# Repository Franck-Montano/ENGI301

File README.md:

# ENGI301
Repository for ENGI301 course work.

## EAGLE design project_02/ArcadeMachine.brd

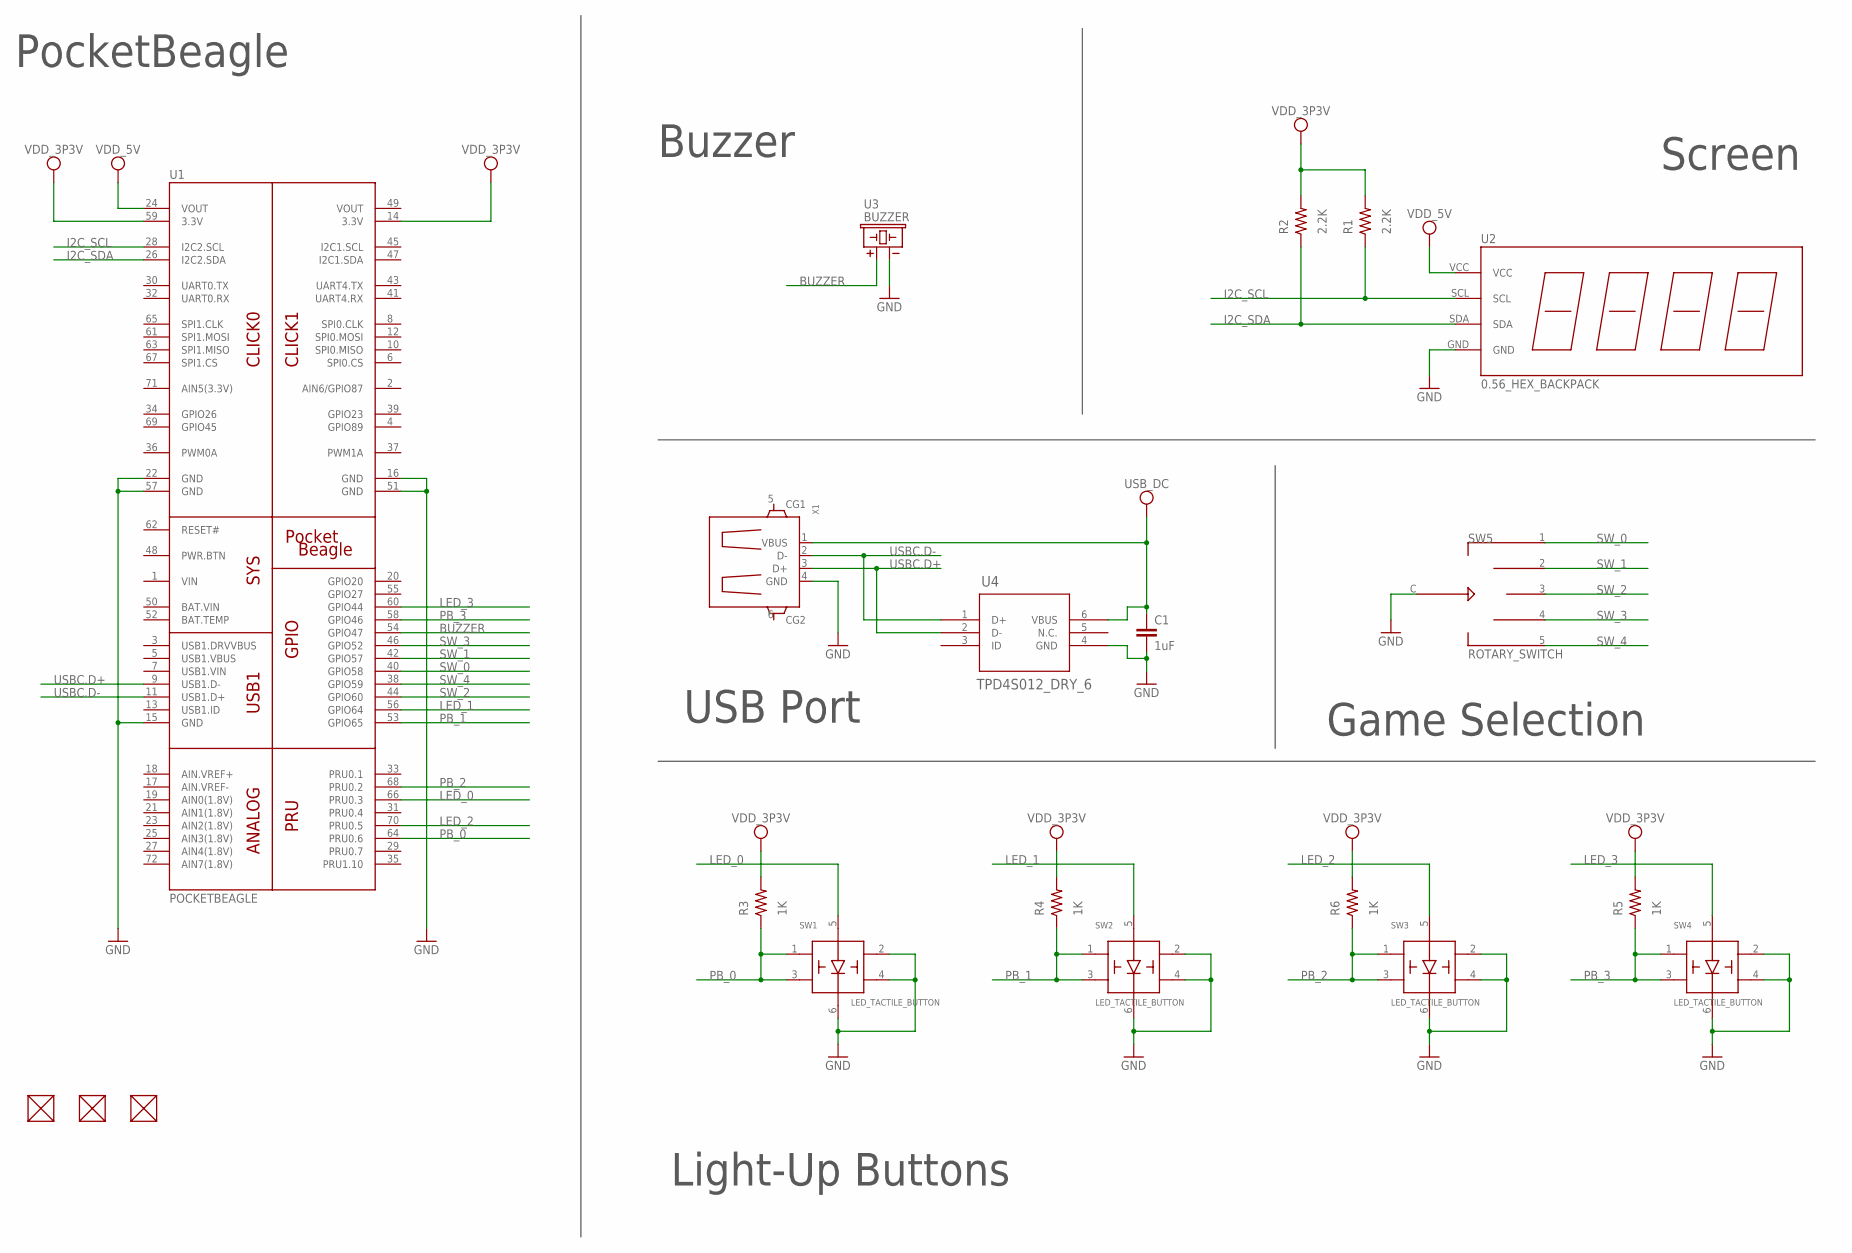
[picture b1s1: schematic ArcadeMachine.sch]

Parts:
C1: 1uF; SPARKFUN-CAPACITORS_0603-CAP
FUD1, FUD2, FUD3: FIDUCIAL; FIDUCIAL_40MIL
R1, R2: 2.2K; R0603
R3, R4, R5, R6: 1K; R0603
SW1, SW2, SW3, SW4: LED_TACTILE_BUTTON
SW5: ROTARY_SWITCH
U1: POCKETBEAGLE
U2: 0.56_HEX_BACKPACK
U3: BUZZER; BUZZER_6.5MM
U4: TPD4S012_DRY_6; BEAGLEBONE_BLUE_DRY6
X1: GHI2_USB_HOST_W/CHASSIS_GND; GHI2_USB_HOST_HORIZONTAL_W/CHASSIS_GND

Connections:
BAT.VIN: U1.50 (BAT.VIN)
BUZZER: U1.54 (GPIO47), U3.+
GND: C1.2, SW1.2, SW1.4, SW1.6, SW2.2, SW2.4, SW2.6, SW3.2, SW3.4, SW3.6, SW4.2, SW4.4, SW4.6, SW5.C, U1.15 (GND), U1.16 (GND), U1.22 (GND), U1.51 (GND), U1.57 (GND), U2.GND, U3.-, U4.4 (GND), X1.4 (GND)
I2C_SCL: R1.1, U1.28 (I2C2.SCL), U2.SCL
I2C_SDA: R2.1, U1.26 (I2C2.SDA), U2.SDA
LED_0: SW1.5, U1.66 (PRU0.3)
LED_1: SW2.5, U1.56 (GPIO64)
LED_2: SW3.5, U1.70 (PRU0.5)
LED_3: SW4.5, U1.60 (GPIO44)
PB_0: R3.1, SW1.1, SW1.3, U1.64 (PRU0.6)
PB_1: R4.1, SW2.1, SW2.3, U1.53 (GPIO65)
PB_2: R6.1, SW3.1, SW3.3, U1.68 (PRU0.2)
PB_3: R5.1, SW4.1, SW4.3, U1.58 (GPIO46)
SW_0: SW5.1, U1.40 (GPIO58)
SW_1: SW5.2, U1.42 (GPIO57)
SW_2: SW5.3, U1.44 (GPIO60)
SW_3: SW5.4, U1.46 (GPIO52)
SW_4: SW5.5, U1.38 (GPIO59)
USBC.D+: U1.9 (USB1.D-), U4.2 (D-), X1.3 (D+)
USBC.D-: U1.11 (USB1.D+), U4.1 (D+), X1.2 (D-)
USB_DC: C1.1, U4.6 (VBUS), X1.1 (VBUS)
VDD_3P3V: R1.2, R2.2, R3.2, R4.2, R5.2, R6.2, U1.14 (3.3V), U1.59 (3.3V)
VDD_5V: U1.24 (VOUT), U2.VCC
VIN: U1.1 (VIN)
VOUT: U1.49 (VOUT)

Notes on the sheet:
Buzzer
Screen
USB Port
Game Selection
Light-Up Buttons
PocketBeagle

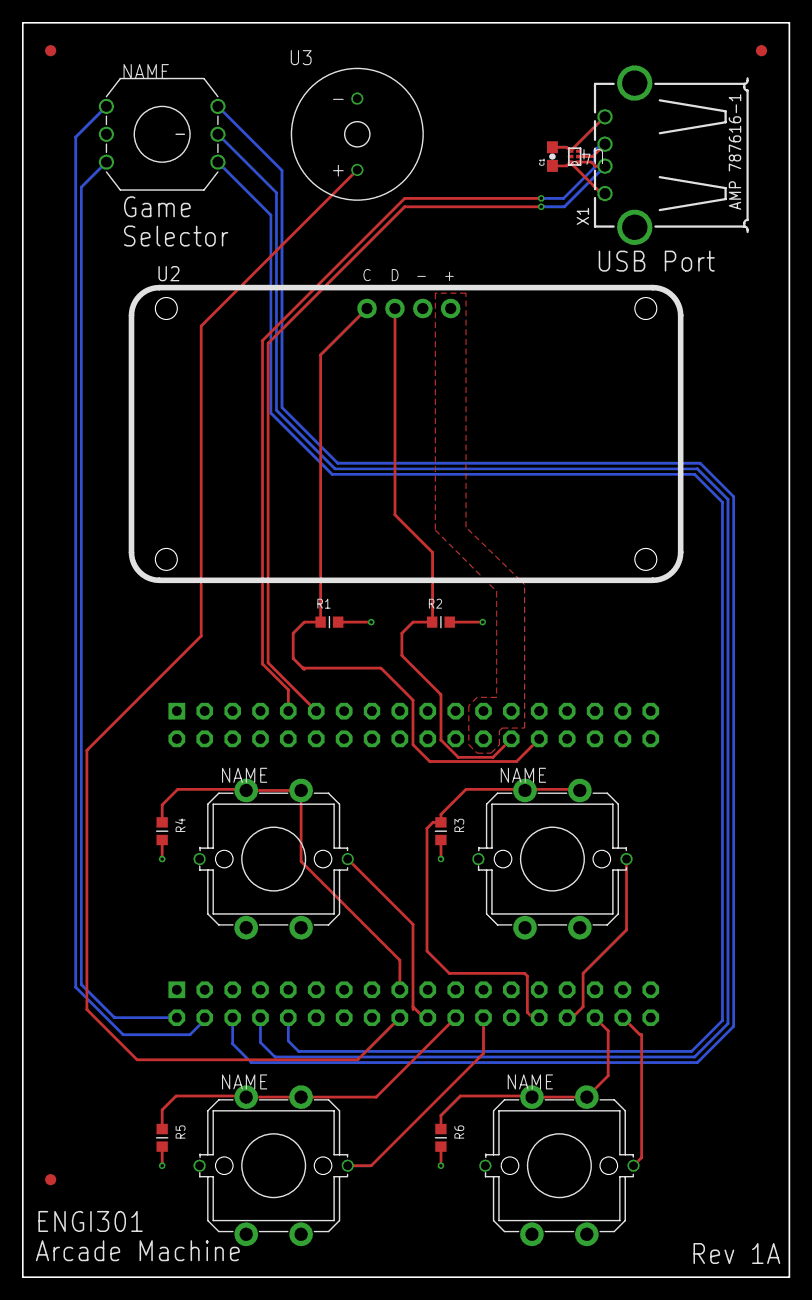
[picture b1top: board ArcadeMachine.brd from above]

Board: 4 copper layers, 69.8 x 114.3 mm, 20 parts (1 on the bottom side), 22 nets.

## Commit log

2018-09-12 Updating README.md
2018-09-27 Added simple calculator (with extra operators)
2018-09-27 Added Python 2 compatibility
2018-09-27 Added blink_USR3 code
2018-09-28 Changed code to fit with in-class example
2018-09-28 Moved constant 'operators' to the Constants category
2018-10-19 Added project powerpoint
2018-10-31 Added base code for arcade machine
2018-11-09 Added working reflex tester code
2018-11-09 Added semi-functioning Simon Says code
2018-11-12 Code is functioning with bugs
2018-11-12 Bugs fixed. Mostly
2018-11-12 Added code to run main code on boot
2018-11-12 Added buzzer compatibility. Most bugs squashed
2018-11-12 Final work code complete. Most bugs hiding. Needs documentation
2018-11-12 Fixed bug caused by using Windows
2018-11-13 Fixed bug caused by using Windows. Added license. Removes extraneous code
2018-11-13 Added Fritzing diagram
2018-11-13 Moved files to new folder
2018-11-13 Added correct README file
2018-11-13 Renamed folder
2018-11-20 Added project 2 proposal (PCB design)
2018-11-21 Added components (multi position switch and USB port). Modified funcional diagram
2018-12-05 Added EAGLE files
2018-12-12 Finished project
